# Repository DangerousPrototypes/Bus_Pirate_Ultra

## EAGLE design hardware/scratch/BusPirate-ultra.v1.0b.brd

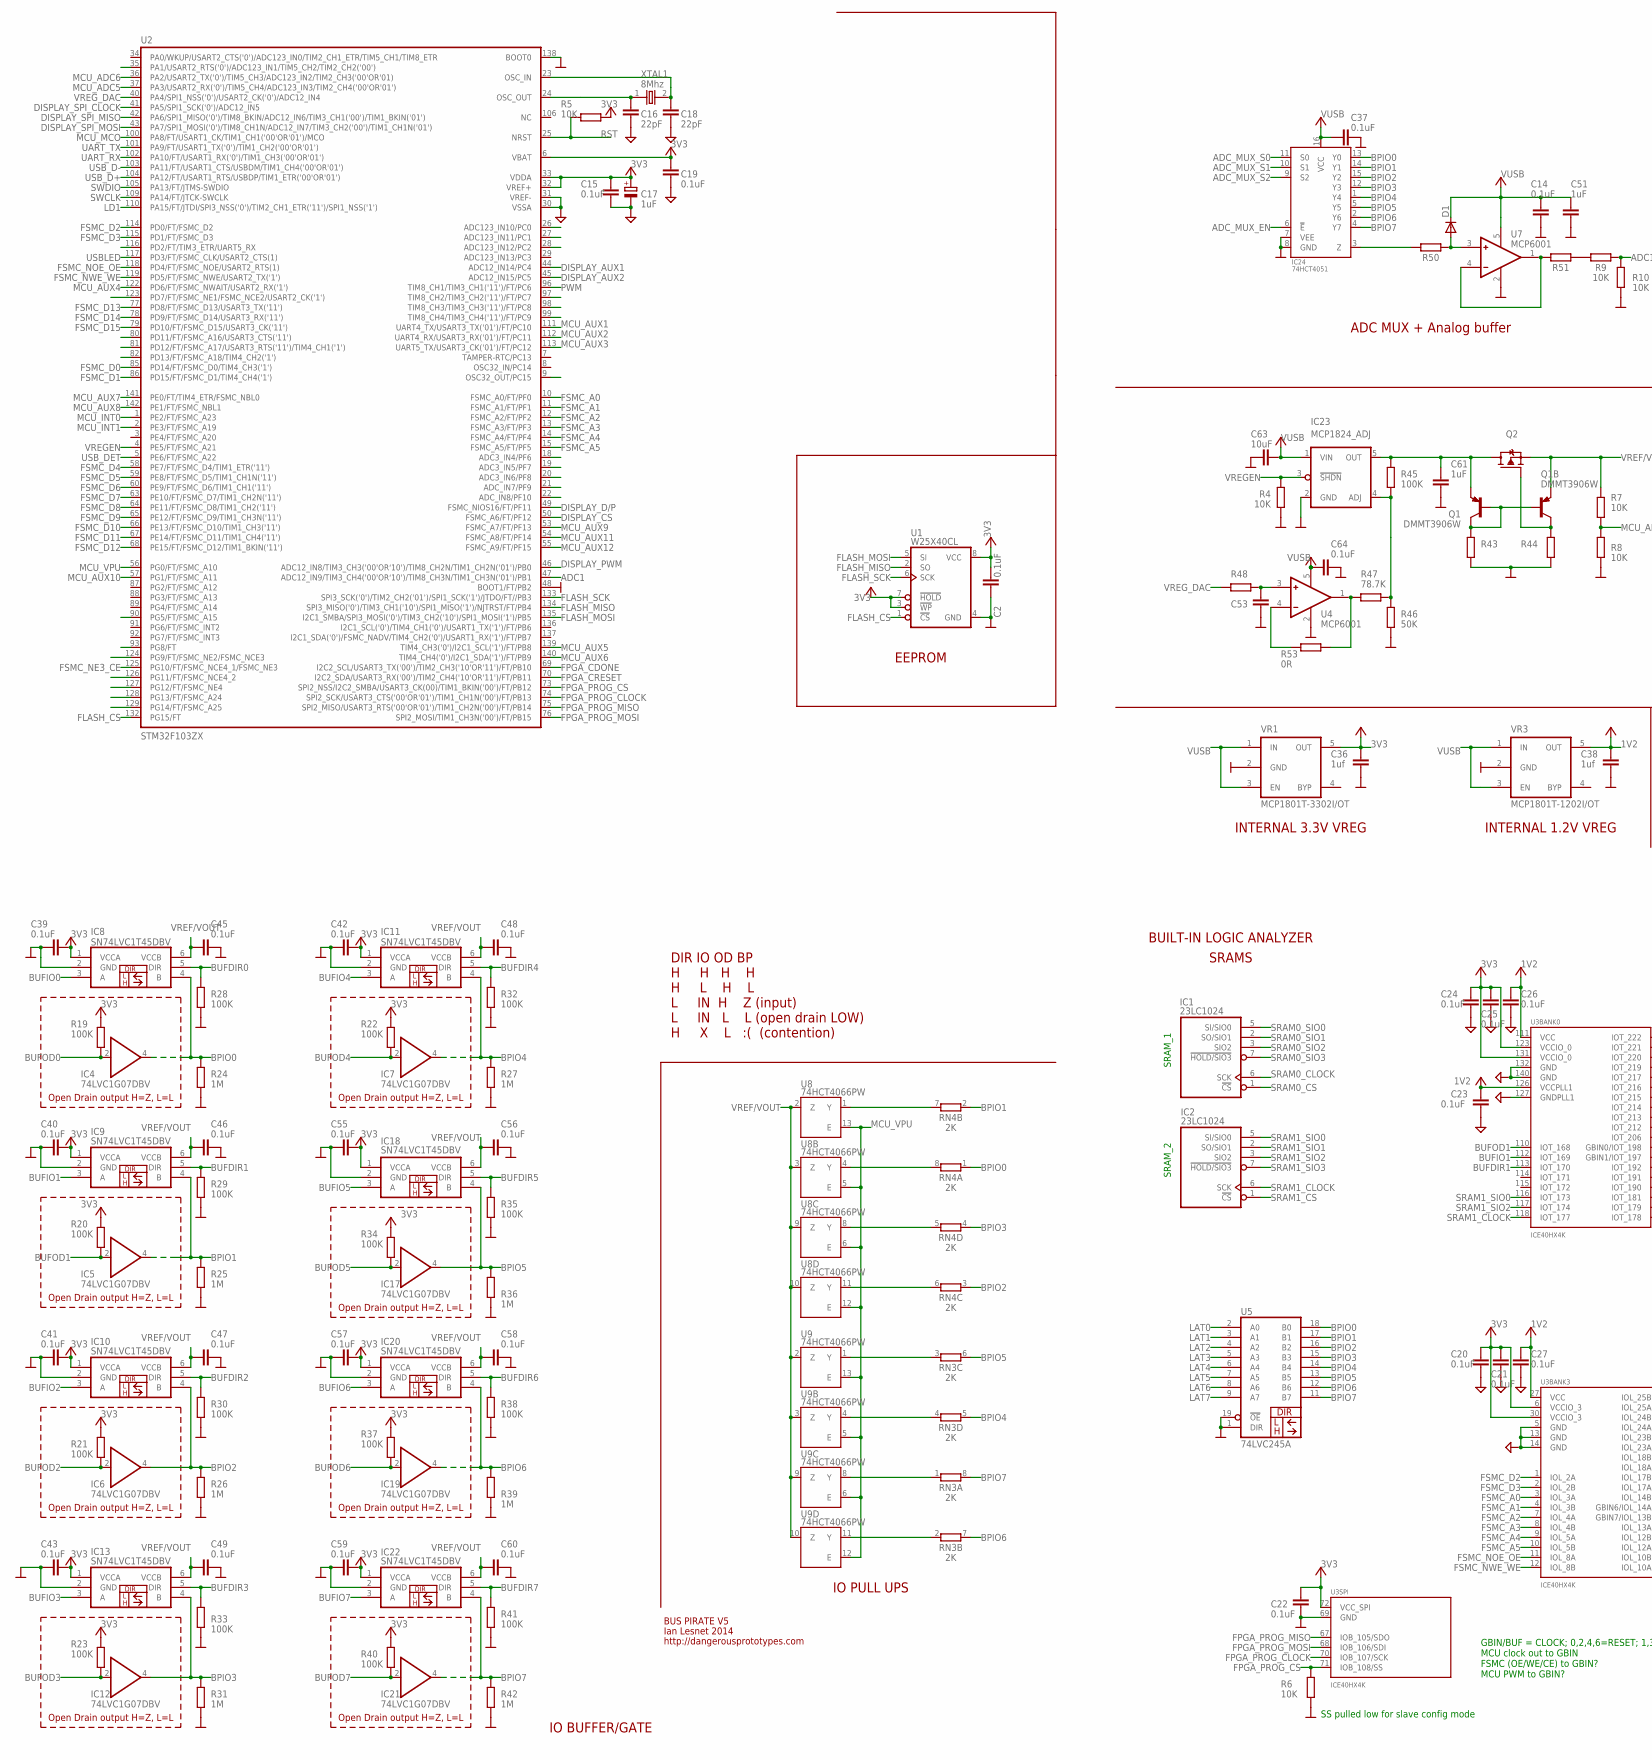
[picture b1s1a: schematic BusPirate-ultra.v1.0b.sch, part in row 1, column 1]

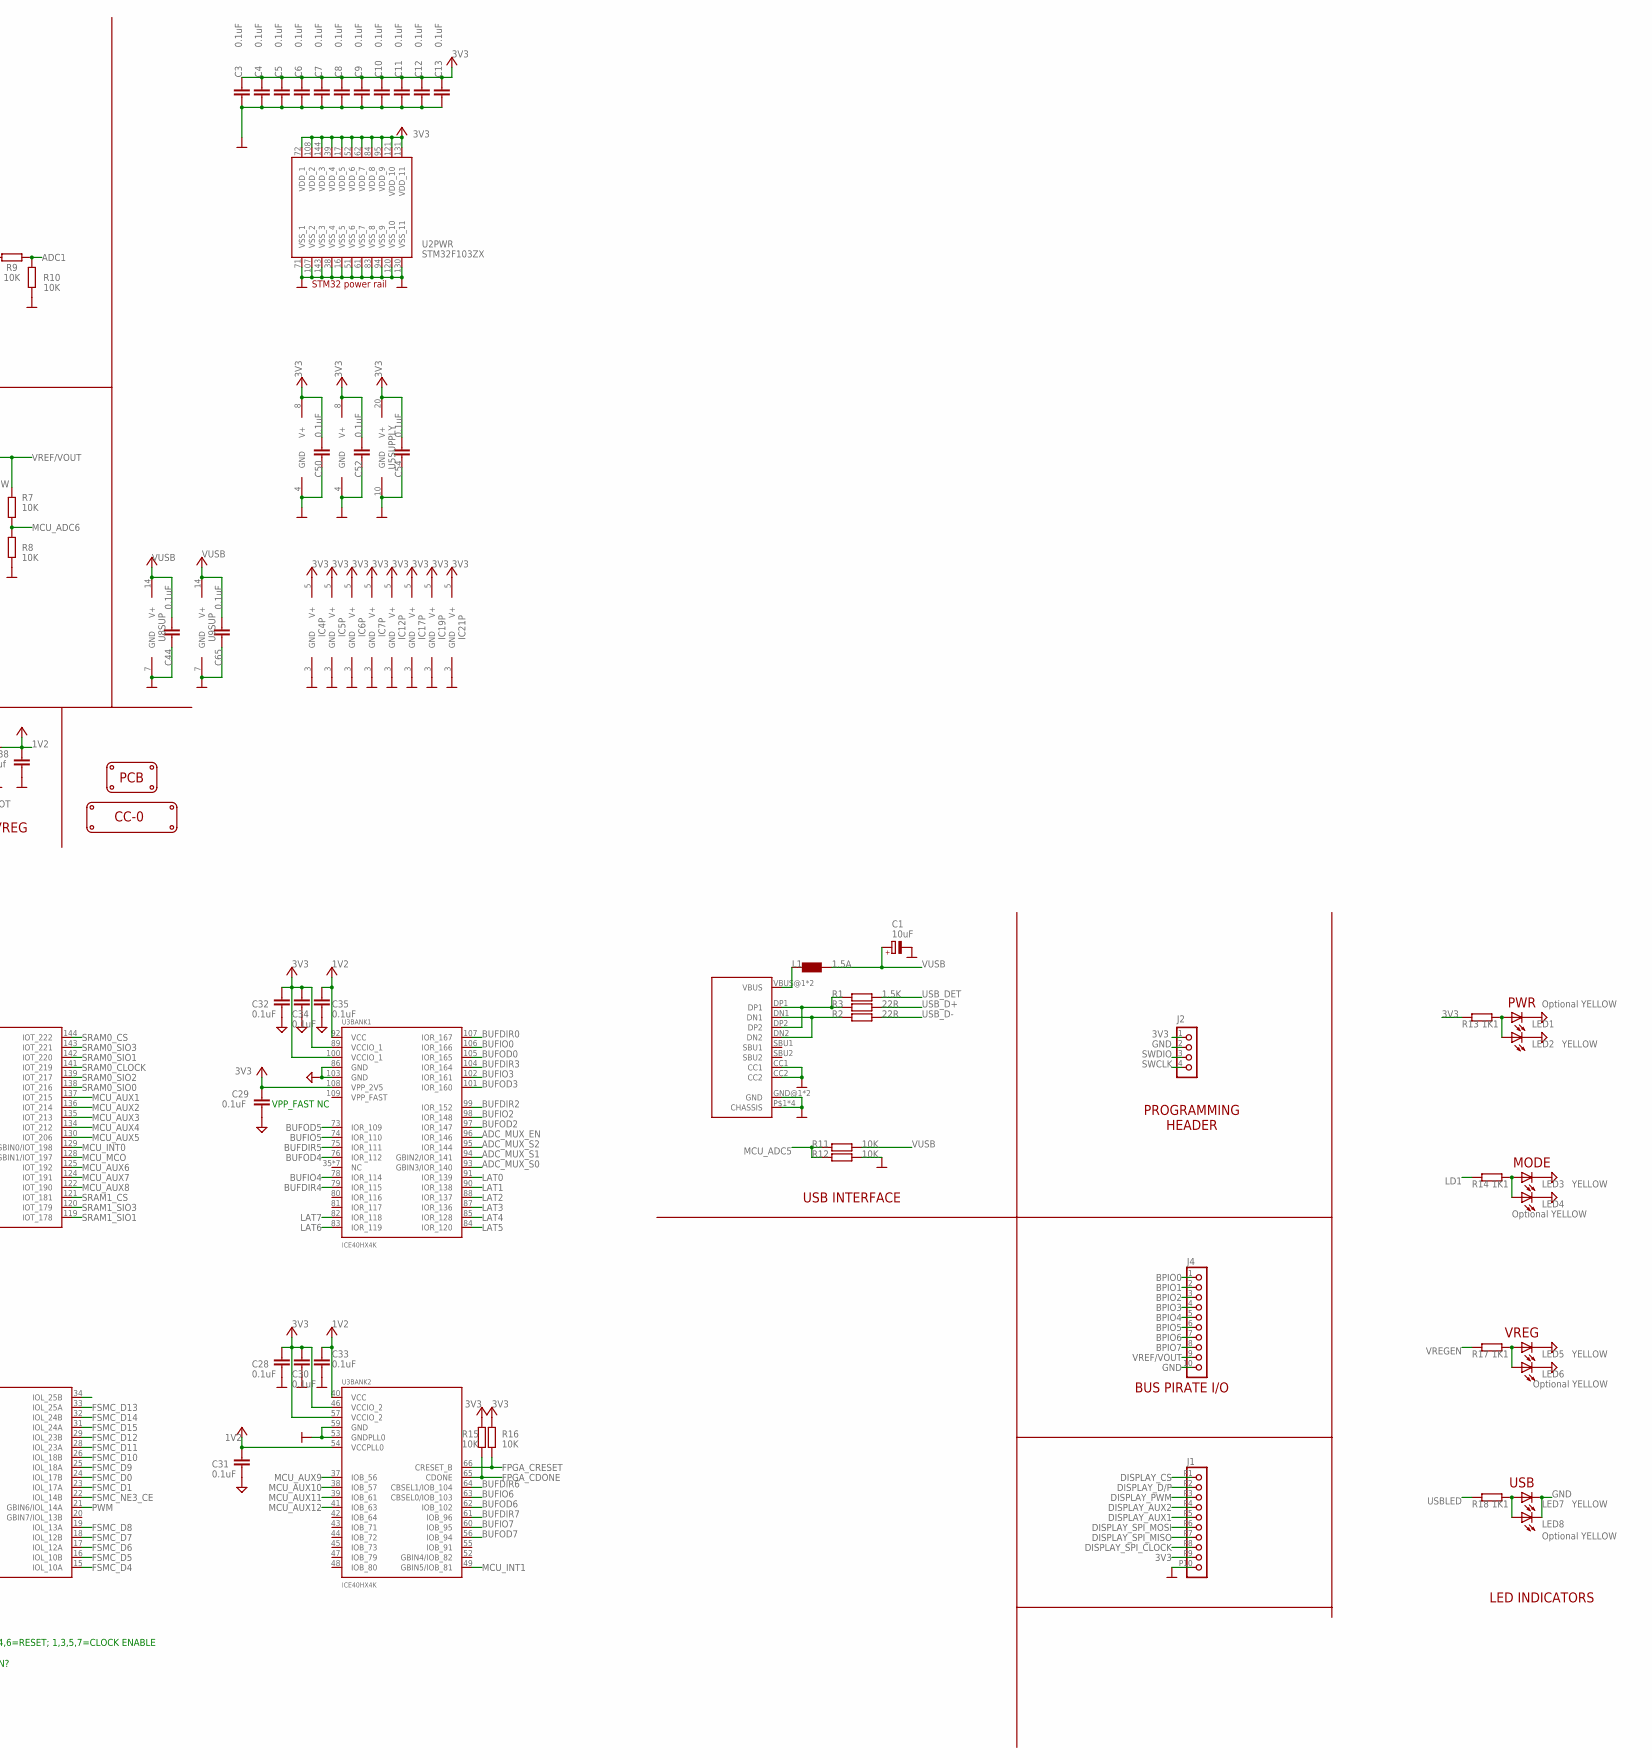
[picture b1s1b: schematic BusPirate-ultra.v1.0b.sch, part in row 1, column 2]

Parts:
C1: 10uF; SMC_A
C2, C3, C4, C5, C6, C7, C8, C9, C11, C12, C13, C14, C15, C19, C21, C22, C23, C24, C25, C26, C28, C29, C30, C31, C32, C33, C34, C35, C37, C44, C50, C52, C54, C65: 0.1uF; C0603
C10, C20, C27: 0.1uF; C402
C16, C18: 22pF; C0603
C17: 1uF; SMC_A
C36, C38: 1uf; C0603
C39, C40, C41, C42, C43, C45, C46, C47, C48, C49, C55, C56, C57, C58, C59, C60: 0.1uF; C0402
C51: 1uF; C0603
C53: CAPACITOR_NPOL-0603; C603
C61: 1uF; C603
C63: 10uF; C603
C64: 0.1uF; C603
D1: DIODE-SOD-123; SOD-123
IC1, IC2: 23LC1024; SOIC-8
IC4, IC5, IC6, IC7, IC12, IC17, IC19, IC21: 74LVC1G07DBV; SC-70-5_EXTENDED_PADS
IC8, IC9, IC10, IC11, IC13, IC18, IC20, IC22: SN74LVC1T45DBV; SC-70-6_EXTENDED_PADS
IC23: MCP1824_ADJ; SOT-23-5
IC24: 74HCT4051; TSSOP-16
J1: CON_MOLEX_MALE_SMT_SH_1.25; MOLEX_533980771
J2: CON_HEADER_1X04; M1X4
J4: CON_HEADER_1X10-RIGHT_ANGLED_PTH_SHROUDED; M1X10_MALE_RIGHT_ANGLES_PTH_SHROUDED
L1: 1.5A; WE-KI_0805_B
LED1, LED4, LED6, LED8: Optional YELLOW; LED-805
LED2, LED3, LED5, LED7: YELLOW; LED-805
LOGO1: LOGO_CC-0
PCB1: PCB_DP_RECTANGLE-50X100; DP10050_V1
Q1: DMMT3906W; SOT-363
Q2: TRANSISTOR_FET_TSM2301CX; SOT-23
R1: 1.5K; R0603
R2, R3: 22R; R0603
R4, R5, R6: 10K; R603
R7, R8, R9, R10, R11, R12, R15, R16: 10K; R0603
R13, R14, R17, R18: 1K1; R603
R19, R20, R21, R22, R23, R28, R29, R30, R32, R33, R34, R35, R37, R38, R40, R41: 100K; R0402
R24, R25, R26, R27, R31, R36, R39, R42: 1M; R0402
R43, R44, R48: RESISTOR-0603; R603
R45: 100K; R603
R46: 50K; R603
R47: 78.7K; R603
R50, R51: R-EU_R0603; R0603
R53: 0R; R603
RN3, RN4: 2K; RN8P-4R-CRA06S
U1: W25X40CL; SOIC-8
U2: STM32F103ZX; TQFP-144
U3: ICE40HX4K; TQFP-144
U4, U7: MCP6001; SOT-23-5
U5: 74LVC245A; TSSOP-20
U8, U9: 74HCT4066PW; TSSOP-14
U$3: USB-C-12; C-31-M-12
VR1: MCP1801T-3302I/OT; SOT-23-5@1
VR3: MCP1801T-1202I/OT; SOT-23-5@1
XTAL1: 8Mhz; XTAL_4X6

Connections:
1V2: C23.2, C26.2, C27.1, C31.2, C33.2, C35.2, C38.1, U3.27 (VCC), U3.40 (VCC), U3.54 (VCCPLL0), U3.92 (VCC), U3.111 (VCC), U3.126 (VCCPLL1), VR3.5 (OUT)
3V3: C2.2, C3.2, C4.2, C5.2, C6.2, C7.2, C8.2, C9.2, C10.1, C11.2, C12.2, C13.2, C15.2, C17.+, C19.2, C20.1, C21.2, C22.2, C24.2, C25.2, C28.2, C29.2, C30.2, C32.2, C34.2, C36.1, C39.1, C40.1, C41.1, C42.1, C43.1, C50.1, C52.1, C54.1, C55.1, C57.1, C59.1, IC1.8 (V+), IC2.8 (V+), IC4.5 (V+), IC5.5 (V+), IC6.5 (V+), IC7.5 (V+), IC8.1 (VCCA), IC9.1 (VCCA), IC10.1 (VCCA), IC11.1 (VCCA), IC12.5 (V+), IC13.1 (VCCA), IC17.5 (V+), IC18.1 (VCCA), IC19.5 (V+), IC20.1 (VCCA), IC21.5 (V+), IC22.1 (VCCA), J1.P9 (9), J2.1, R5.2, R13.2, R15.2, R16.2, R19.2, R20.2, R21.2, R22.2, R23.2, R34.2, R37.2, R40.2, U1.3 (!WP), U1.7 (!HOLD), U1.8 (VCC), U2.6 (VBAT), U2.17 (VDD_5), U2.32 (VREF+), U2.33 (VDDA), U2.39 (VDD_4), U2.52 (VDD_6), U2.62 (VDD_7), U2.72 (VDD_1), U2.84 (VDD_8), U2.95 (VDD_9), U2.108 (VDD_2), U2.121 (VDD_10), U2.131 (VDD_11), U2.144 (VDD_3), U3.6 (VCCIO_3), U3.30 (VCCIO_3), U3.46 (VCCIO_2), U3.57 (VCCIO_2), U3.72 (VCC_SPI), U3.89 (VCCIO_1), U3.100 (VCCIO_1), U3.108 (VPP_2V5), U3.123 (VCCIO_0), U3.131 (VCCIO_0), U5.20 (V+), VR1.5 (OUT)
ADC1: R9.2, R10.2, U2.47 (ADC12_IN9/TIM3_CH4('00'OR'10')/TIM8_CH3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)
ADC_MUX_EN: IC24.6 (!E), U3.96 (IOR_146)
ADC_MUX_S0: IC24.11 (S0), U3.93 (GBIN3/IOR_140)
ADC_MUX_S1: IC24.10 (S1), U3.94 (GBIN2/IOR_141)
ADC_MUX_S2: IC24.9 (S2), U3.95 (IOR_144)
BPIO0: IC4.4 (O), IC8.4 (B), IC24.13 (Y0), J4.1, R24.2, RN4.1, U5.18 (B0)
BPIO1: IC5.4 (O), IC9.4 (B), IC24.14 (Y1), J4.2, R25.2, RN4.2 (1), U5.17 (B1)
BPIO2: IC6.4 (O), IC10.4 (B), IC24.15 (Y2), J4.3, R26.2, RN4.3 (1), U5.16 (B2)
BPIO3: IC12.4 (O), IC13.4 (B), IC24.12 (Y3), J4.4, R31.2, RN4.4 (1), U5.15 (B3)
BPIO4: IC7.4 (O), IC11.4 (B), IC24.1 (Y4), J4.5, R27.2, RN3.5 (2), U5.14 (B4)
BPIO5: IC17.4 (O), IC18.4 (B), IC24.5 (Y5), J4.6, R36.2, RN3.6 (2), U5.13 (B5)
BPIO6: IC19.4 (O), IC20.4 (B), IC24.2 (Y6), J4.7, R39.2, RN3.7 (2), U5.12 (B6)
BPIO7: IC21.4 (O), IC22.4 (B), IC24.4 (Y7), J4.8, R42.2, RN3.8 (2), U5.11 (B7)
BUFDIR0: IC8.5 (DIR), R28.2, U3.107 (IOR_167)
BUFDIR1: IC9.5 (DIR), R29.2, U3.113 (IOT_170)
BUFDIR2: IC10.5 (DIR), R30.2, U3.99 (IOR_152)
BUFDIR3: IC13.5 (DIR), R33.2, U3.104 (IOR_164)
BUFDIR4: IC11.5 (DIR), R32.2, U3.79 (IOR_115)
BUFDIR5: IC18.5 (DIR), R35.2, U3.75 (IOR_111)
BUFDIR6: IC20.5 (DIR), R38.2, U3.64 (CBSEL1/IOB_104)
BUFDIR7: IC22.5 (DIR), R41.2, U3.61 (IOB_96)
BUFIO0: IC8.3 (A), U3.106 (IOR_166)
BUFIO1: IC9.3 (A), U3.112 (IOT_169)
BUFIO2: IC10.3 (A), U3.98 (IOR_148)
BUFIO3: IC13.3 (A), U3.102 (IOR_161)
BUFIO4: IC11.3 (A), U3.78 (IOR_114)
BUFIO5: IC18.3 (A), U3.74 (IOR_110)
BUFIO6: IC20.3 (A), U3.63 (CBSEL0/IOB_103)
BUFIO7: IC22.3 (A), U3.60 (IOB_95)
BUFOD0: IC4.2 (I), R19.1, U3.105 (IOR_165)
BUFOD1: IC5.2 (I), R20.1, U3.110 (IOT_168)
BUFOD2: IC6.2 (I), R21.1, U3.97 (IOR_147)
BUFOD3: IC12.2 (I), R23.1, U3.101 (IOR_160)
BUFOD4: IC7.2 (I), R22.1, U3.76 (IOR_112)
BUFOD5: IC17.2 (I), R34.1, U3.73 (IOR_109)
BUFOD6: IC19.2 (I), R37.1, U3.62 (IOB_102)
BUFOD7: IC21.2 (I), R40.1, U3.56 (IOB_94)
D+: R1.1, R3.2, U$3.DP1, U$3.DP2
D-: R2.2, U$3.DN1, U$3.DN2
DISPLAY_AUX1: J1.P5 (5), U2.44 (ADC12_IN14/PC4)
DISPLAY_AUX2: J1.P4 (4), U2.45 (ADC12_IN15/PC5)
DISPLAY_CS: J1.P1 (1), U2.50 (FSMC_A6/FT/PF12)
DISPLAY_D/P: J1.P2 (2), U2.49 (FSMC_NIOS16/FT/PF11)
DISPLAY_PWM: J1.P3 (3), U2.46 (ADC12_IN8/TIM3_CH3('00'OR'10')/TIM8_CH2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)
DISPLAY_SPI_CLOCK: J1.P8 (8), U2.41 (PA5/SPI1_SCK('0')/ADC12_IN5)
DISPLAY_SPI_MISO: J1.P7 (7), U2.42 (PA6/SPI1_MISO('0')/TIM8_BKIN/ADC12_IN6/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)
DISPLAY_SPI_MOSI: J1.P6 (6), U2.43 (PA7/SPI1_MOSI('0')/TIM8_CH1N/ADC12_IN7/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)
FLASH_CS: U1.1 (!CS), U2.132 (PG15/FT)
FLASH_MISO: U1.2 (SO), U2.134 (SPI3_MISO('0')/TIM3_CH1('10')/SPI1_MISO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)
FLASH_MOSI: U1.5 (SI), U2.135 (I2C1_SMBA/SPI3_MOSI('0')/TIM3_CH2('10')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)
FLASH_SCK: U1.6 (SCK), U2.133 (SPI3_SCK('0')/TIM2_CH2('01')/SPI1_SCK('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)
FPGA_CDONE: R15.1, U2.69 (I2C2_SCL/USART3_TX('00')/TIM2_CH3('10'O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), U3.65 (CDONE)
FPGA_CRESET: R16.1, U2.70 (I2C2_SDA/USART3_RX('00')/TIM2_CH4('10'O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), U3.66 (CRESET_B)
FPGA_PROG_CLOCK: U2.74 (SPI2_SCK/USART3_CTS('00'OR'01')/TIM1_CH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), U3.70 (IOB_107/SCK)
FPGA_PROG_CS: R6.1, U2.73 (SPI2_NSS/I2C2_SMBA/USART3_CK(00)/TIM1_B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), U3.71 (IOB_108/SS)
FPGA_PROG_MISO: U2.75 (SPI2_MISO/USART3_RTS('00'OR'01')/TIM1_C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), U3.67 (IOB_105/SDO)
FPGA_PROG_MOSI: U2.76 (SPI2_MOSI/TIM1_CH3N('00')/FT/PB15), U3.68 (IOB_106/SDI)
FSMC_A0: U2.10 (FSMC_A0/FT/PF0), U3.3 (IOL_3A)
FSMC_A1: U2.11 (FSMC_A1/FT/PF1), U3.4 (IOL_3B)
FSMC_A2: U2.12 (FSMC_A2/FT/PF2), U3.7 (IOL_4A)
FSMC_A3: U2.13 (FSMC_A3/FT/PF3), U3.8 (IOL_4B)
FSMC_A4: U2.14 (FSMC_A4/FT/PF4), U3.9 (IOL_5A)
FSMC_A5: U2.15 (FSMC_A5/FT/PF5), U3.10 (IOL_5B)
FSMC_D0: U2.85 (PD14/FT/FSMC_D0/TIM4_CH3('1')), U3.24 (IOL_17B)
FSMC_D1: U2.86 (PD15/FT/FSMC_D1/TIM4_CH4('1')), U3.23 (IOL_17A)
FSMC_D2: U2.114 (PD0/FT/FSMC_D2), U3.1 (IOL_2A)
FSMC_D3: U2.115 (PD1/FT/FSMC_D3), U3.2 (IOL_2B)
FSMC_D4: U2.58 (PE7/FT/FSMC_D4/TIM1_ETR('11')), U3.15 (IOL_10A)
FSMC_D5: U2.59 (PE8/FT/FSMC_D5/TIM1_CH1N('11')), U3.16 (IOL_10B)
FSMC_D6: U2.60 (PE9/FT/FSMC_D6/TIM1_CH1('11')), U3.17 (IOL_12A)
FSMC_D7: U2.63 (PE10/FT/FSMC_D7/TIM1_CH2N('11')), U3.18 (IOL_12B)
FSMC_D8: U2.64 (PE11/FT/FSMC_D8/TIM1_CH2('11')), U3.19 (IOL_13A)
FSMC_D9: U2.65 (PE12/FT/FSMC_D9/TIM1_CH3N('11')), U3.25 (IOL_18A)
FSMC_D10: U2.66 (PE13/FT/FSMC_D10/TIM1_CH3('11')), U3.26 (IOL_18B)
FSMC_D11: U2.67 (PE14/FT/FSMC_D11/TIM1_CH4('11')), U3.28 (IOL_23A)
FSMC_D12: U2.68 (PE15/FT/FSMC_D12/TIM1_BKIN('11')), U3.29 (IOL_23B)
FSMC_D13: U2.77 (PD8/FT/FSMC_D13/USART3_TX('11')), U3.33 (IOL_25A)
FSMC_D14: U2.78 (PD9/FT/FSMC_D14/USART3_RX('11')), U3.32 (IOL_24B)
FSMC_D15: U2.79 (PD10/FT/FSMC_D15/USART3_CK('11')), U3.31 (IOL_24A)
FSMC_NE3_CE: U2.125 (PG10/FT/FSMC_NCE4_1/FSMC_NE3), U3.22 (IOL_14B)
FSMC_NOE_OE: U2.118 (PD4/FT/FSMC_NOE/USART2_RTS(1)), U3.11 (IOL_8A)
FSMC_NWE_WE: U2.119 (PD5/FT/FSMC_NWE/USART2_TX('1')), U3.12 (IOL_8B)
GND: C1.-, C2.1, C3.1, C4.1, C5.1, C6.1, C7.1, C8.1, C9.1, C10.2, C11.1, C12.1, C13.1, C14.2, C15.1, C16.1, C17.-, C18.1, C19.1, C20.2, C21.1, C22.1, C23.1, C24.1, C25.1, C26.1, C27.2, C28.1, C29.1, C30.1, C31.1, C32.1, C33.1, C34.1, C35.1, C36.2, C37.2, C38.2, C39.2, C40.2, C41.2, C42.2, C43.2, C44.2, C45.1, C46.1, C47.1, C48.1, C49.1, C50.2, C51.2, C52.2, C53.2, C54.2, C55.2, C56.1, C57.2, C58.1, C59.2, C60.1, C61.2, C63.2, C64.2, C65.2, IC1.4 (GND), IC2.4 (GND), IC4.3 (GND), IC5.3 (GND), IC6.3 (GND), IC7.3 (GND), IC8.2 (GND), IC9.2 (GND), IC10.2 (GND), IC11.2 (GND), IC12.3 (GND), IC13.2 (GND), IC17.3 (GND), IC18.2 (GND), IC19.3 (GND), IC20.2 (GND), IC21.3 (GND), IC22.2 (GND), IC23.2 (GND), IC24.7 (VEE), IC24.8 (GND), J1.P10 (10), J2.2, J4.10, LED1.C, LED2.C, LED3.C, LED4.C, LED5.C, LED6.C, LED7.C, LED8.C, R4.2, R6.2, R8.1, R10.1, R12.1, R24.1, R25.1, R26.1, R27.1, R28.1, R29.1, R30.1, R31.1, R32.1, R33.1, R35.1, R36.1, R38.1, R39.1, R41.1, R42.1, R43.1, R44.1, R46.2, U1.4 (GND), U2.16 (VSS_5), U2.30 (VSSA), U2.31 (VREF-), U2.38 (VSS_4), U2.48 (BOOT1/FT/PB2), U2.51 (VSS_6), U2.61 (VSS_7), U2.71 (VSS_1), U2.83 (VSS_8), U2.94 (VSS_9), U2.107 (VSS_2), U2.120 (VSS_10), U2.130 (VSS_11), U2.138 (BOOT0), U2.143 (VSS_3), U3.5 (GND), U3.13 (GND), U3.14 (GND), U3.53 (GNDPLL0), U3.59 (GND), U3.69 (GND), U3.86 (GND), U3.103 (GND), U3.127 (GNDPLL1), U3.132 (GND), U3.140 (GND), U4.2 (V-), U5.1 (DIR), U5.10 (GND), U5.19 (!OE), U7.2 (V-), U8.7 (GND), U9.7 (GND), U$3.CC1, U$3.CC2, U$3.GND@1 (GND), U$3.GND@2 (GND), U$3.P$1 (CHASSIS), U$3.P$2 (CHASSIS), U$3.P$3 (CHASSIS), U$3.P$4 (CHASSIS), VR1.2 (GND), VR3.2 (GND)
LAT0: U3.91 (IOR_139), U5.2 (A0)
LAT1: U3.90 (IOR_138), U5.3 (A1)
LAT2: U3.88 (IOR_137), U5.4 (A2)
LAT3: U3.87 (IOR_136), U5.5 (A3)
LAT4: U3.85 (IOR_128), U5.6 (A4)
LAT5: U3.84 (IOR_120), U5.7 (A5)
LAT6: U3.83 (IOR_119), U5.8 (A6)
LAT7: U3.82 (IOR_118), U5.9 (A7)
LD1: R14.2, U2.110 (PA15/FT/JTDI/SPI3_NSS('0')/TIM2_CH1_ETR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)
MCU_ADC5: R11.2, R12.2, U2.37 (PA3/USART2_RX('0')/TIM5_CH4/ADC123_IN3/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)
MCU_ADC6: R7.2, R8.2, U2.36 (PA2/USART2_TX('0')/TIM5_CH3/ADC123_IN2/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)
MCU_AUX1: U2.111 (UART4_TX/USART3_TX('01')/FT/PC10), U3.137 (IOT_215)
MCU_AUX2: U2.112 (UART4_RX/USART3_RX('01')/FT/PC11), U3.136 (IOT_214)
MCU_AUX3: U2.113 (UART5_TX/USART3_CK('01')/FT/PC12), U3.135 (IOT_213)
MCU_AUX4: U2.122 (PD6/FT/FSMC_NWAIT/USART2_RX('1')), U3.134 (IOT_212)
MCU_AUX5: U2.139 (TIM4_CH3('0')/I2C1_SCL('1')/FT/PB8), U3.130 (IOT_206)
MCU_AUX6: U2.140 (TIM4_CH4('0')/I2C1_SDA('1')/FT/PB9), U3.125 (IOT_192)
MCU_AUX7: U2.141 (PE0/FT/TIM4_ETR/FSMC_NBL0), U3.124 (IOT_191)
MCU_AUX8: U2.142 (PE1/FT/FSMC_NBL1), U3.122 (IOT_190)
MCU_AUX9: U2.53 (FSMC_A7/FT/PF13), U3.37 (IOB_56)
MCU_AUX10: U2.57 (PG1/FT/FSMC_A11), U3.38 (IOB_57)
MCU_AUX11: U2.54 (FSMC_A8/FT/PF14), U3.39 (IOB_61)
MCU_AUX12: U2.55 (FSMC_A9/FT/PF15), U3.41 (IOB_63)
MCU_INT0: U2.1 (PE2/FT/FSMC_A23), U3.129 (GBIN0/IOT_198)
MCU_INT1: U2.2 (PE3/FT/FSMC_A19), U3.49 (GBIN5/IOB_81)
MCU_MCO: U2.100 (PA8/FT/USART1_CK/TIM1_CH1('00'OR'01')/M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), U3.128 (GBIN1/IOT_197)
MCU_VPU: U2.56 (PG0/FT/FSMC_A10), U8.5 (E), U8.6 (E), U8.12 (E), U8.13 (E), U9.5 (E), U9.6 (E), U9.12 (E), U9.13 (E)
unnamed: L1.2 (1), U$3.VBUS@1 (VBUS), U$3.VBUS@2 (VBUS)
unnamed: RN4.7 (2), U8.1 (Y)
unnamed: RN4.8 (2), U8.4 (Y)
unnamed: RN4.5 (2), U8.8 (Y)
unnamed: RN4.6 (2), U8.11 (Y)
unnamed: LED3.A, LED4.A, R14.1
unnamed: LED1.A, LED2.A, R13.1
unnamed: C18.2, U2.23 (OSC_IN), XTAL1.2
unnamed: C16.2, U2.24 (OSC_OUT), XTAL1.1
unnamed: Q1.6 (C), Q2.1 (G), R44.2
unnamed: IC23.4 (ADJ), R45.1, R46.1, R47.2
unnamed: LED7.A, LED8.A, R18.1
unnamed: R53.1, U4.4 (-)
unnamed: LED5.A, LED6.A, R17.1
unnamed: R47.1, R53.2, U4.1 (OUT)
unnamed: C61.1, IC23.5 (OUT), Q1.4 (E), Q2.3 (D), R45.2
unnamed: Q1.1 (B), Q1.2 (B), Q1.3 (C), R43.2
unnamed: C53.1, R48.2, U4.3 (+)
unnamed: D1.A, R50.2, U7.3 (+)
unnamed: RN3.3 (1), U9.1 (Y)
unnamed: RN3.4 (1), U9.4 (Y)
unnamed: RN3.1, U9.8 (Y)
unnamed: RN3.2 (1), U9.11 (Y)
unnamed: IC24.3 (Z), R50.1
unnamed: R51.1, U7.1 (OUT), U7.4 (-)
unnamed: R9.1, R51.2
PWM: U2.96 (TIM8_CH1/TIM3_CH1('11')/FT/PC6), U3.21 (GBIN6/IOL_14A)
RST: R5.1, U2.25 (NRST)
SRAM0_CLOCK: IC1.6 (SCK), U3.141 (IOT_219)
SRAM0_CS: IC1.1 (!CS), U3.144 (IOT_222)
SRAM0_SIO0: IC1.5 (SI/SIO0), U3.138 (IOT_216)
SRAM0_SIO1: IC1.2 (SO/SIO1), U3.142 (IOT_220)
SRAM0_SIO2: IC1.3 (SIO2), U3.139 (IOT_217)
SRAM0_SIO3: IC1.7 (!HOLD/SIO3), U3.143 (IOT_221)
SRAM1_CLOCK: IC2.6 (SCK), U3.118 (IOT_177)
SRAM1_CS: IC2.1 (!CS), U3.121 (IOT_181)
SRAM1_SIO0: IC2.5 (SI/SIO0), U3.116 (IOT_173)
SRAM1_SIO1: IC2.2 (SO/SIO1), U3.119 (IOT_178)
SRAM1_SIO2: IC2.3 (SIO2), U3.117 (IOT_174)
SRAM1_SIO3: IC2.7 (!HOLD/SIO3), U3.120 (IOT_179)
SWCLK: J2.4, U2.109 (PA14/FT/JTCK-SWCLK)
SWDIO: J2.3, U2.105 (PA13/FT/JTMS-SWDIO)
UART_RX: U2.102 (PA10/FT/USART1_RX('0')/TIM1_CH3('00'OR'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)
UART_TX: U2.101 (PA9/FT/USART1_TX('0')/TIM1_CH2('00'OR'0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)
USBLED: R18.2, U2.117 (PD3/FT/FSMC_CLK/USART2_CTS(1))
USB_D+: R3.1, U2.104 (PA12/FT/USART1_RTS/USBDP/TIM1_ETR('00'O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)
USB_D-: R2.1, U2.103 (PA11/FT/USART1_CTS/USBDM/TIM1_CH4('00'O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)
USB_DET: R1.2, U2.5 (PE6/FT/FSMC_A22)
VPP_FAST: U3.109 (VPP_FAST)
VREF/VOUT: C45.2, C46.2, C47.2, C48.2, C49.2, C56.2, C58.2, C60.2, IC8.6 (VCCB), IC9.6 (VCCB), IC10.6 (VCCB), IC11.6 (VCCB), IC13.6 (VCCB), IC18.6 (VCCB), IC20.6 (VCCB), IC22.6 (VCCB), J4.9, Q1.5 (E), Q2.2 (S), R7.1, U8.2 (Z), U8.3 (Z), U8.9 (Z), U8.10 (Z), U9.2 (Z), U9.3 (Z), U9.9 (Z), U9.10 (Z)
VREGEN: IC23.3 (!SHDN), R4.1, R17.2, U2.4 (PE5/FT/FSMC_A21)
VREG_DAC: R48.1, U2.40 (PA4/SPI1_NSS('0')/USART2_CK('0')/ADC12_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)
VUSB: C1.+, C14.1, C37.1, C44.1, C51.1, C63.1, C64.1, C65.1, D1.C, IC23.1 (VIN), IC24.16 (VCC), L1.1 (2), R11.1, U4.5 (V+), U7.5 (V+), U8.14 (V+), U9.14 (V+), VR1.1 (IN), VR1.3 (EN), VR3.1 (IN), VR3.3 (EN)

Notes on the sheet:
BUS PIRATE V5
Ian Lesnet 2014
http://dangerousprototypes.com
SRAMS
IO BUFFER/GATE
BUS PIRATE I/O
PWR
MODE
VREG
PROGRAMMING HEADER
USB
INTERNAL 3.3V VREG
BUILT-IN LOGIC ANALYZER
ADC MUX + Analog buffer
USB INTERFACE
IO PULL UPS
LED INDICATORS
Open Drain output H=Z, L=L
SS pulled low for slave config mode
VPP_FAST NC
GBIN/BUF = CLOCK; 0,2,4,6=RESET; 1,3,5,7=CLOCK ENABLE MCU clock out to GBIN FSMC (OE/WE/CE) to GBIN? MCU PWM to GBIN?
DIR IO OD BP H H H H H L H L L IN H Z (input) L IN L L (open drain LOW) H X L :( (contention)
STM32 power rail
INTERNAL 1.2V VREG
SRAM_1
SRAM_2
EEPROM

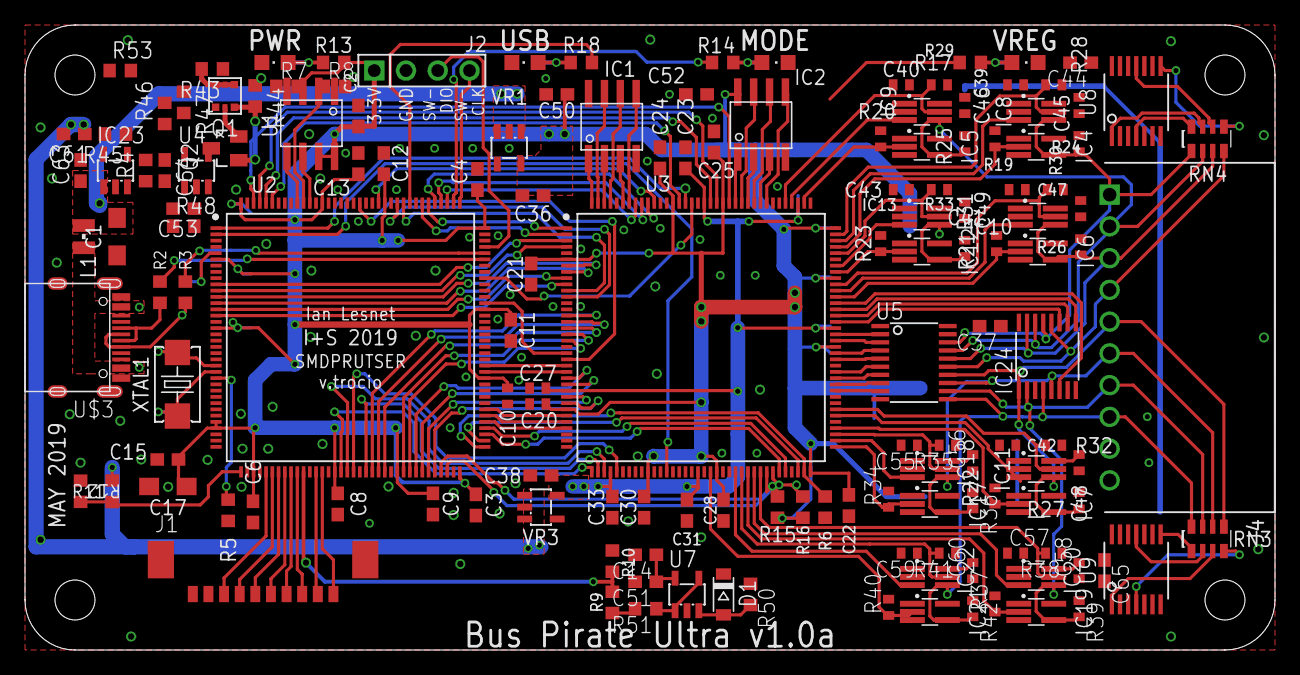
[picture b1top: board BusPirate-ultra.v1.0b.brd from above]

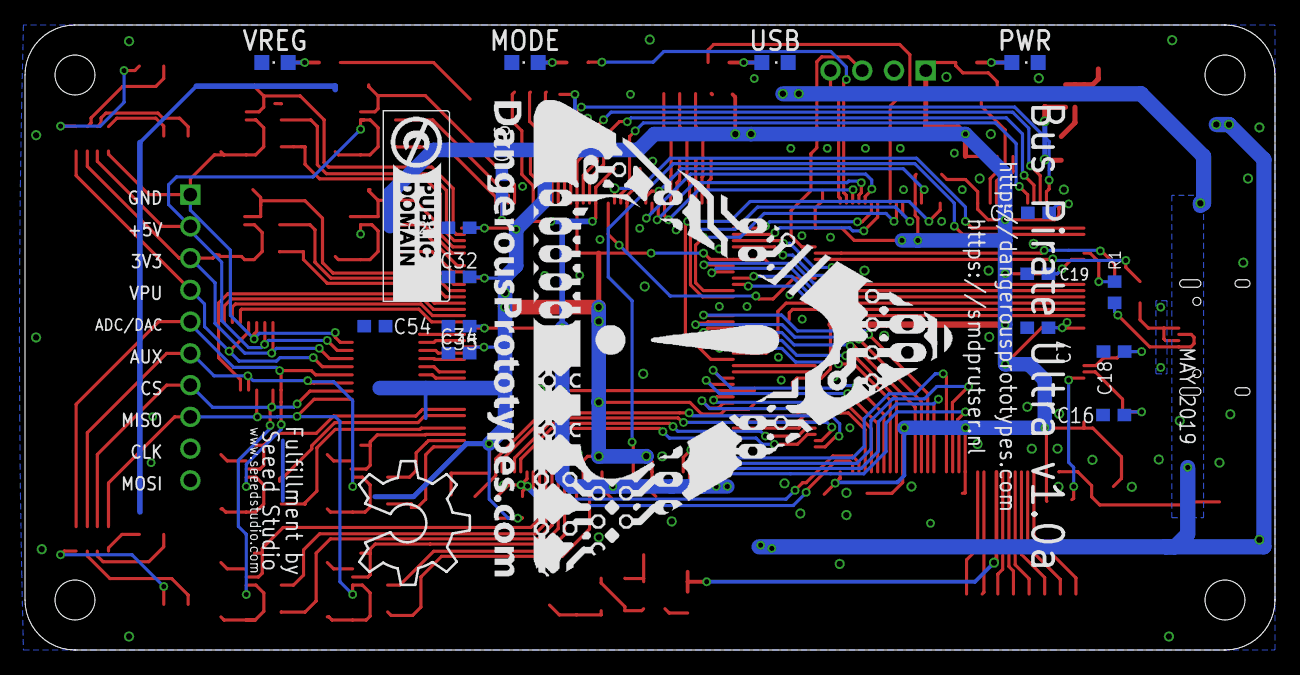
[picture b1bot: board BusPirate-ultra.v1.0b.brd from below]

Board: 2 copper layers, 100.0 x 50.0 mm, 169 parts (19 on the bottom side), 162 nets.

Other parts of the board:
U$1: DP-LOGO
U$2: OSHW_8X350_NOTEXT
U$4: DP_LOGO_ART_1.5X1.5

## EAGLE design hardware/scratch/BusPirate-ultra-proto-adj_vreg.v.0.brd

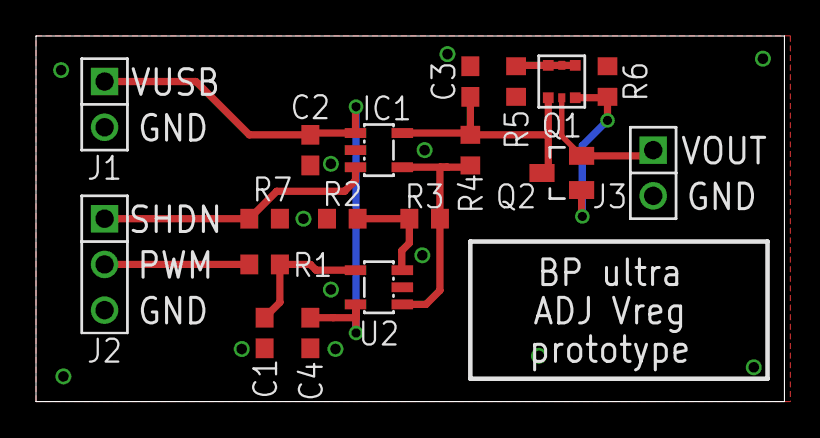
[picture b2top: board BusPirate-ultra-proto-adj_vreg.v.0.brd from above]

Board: 2 copper layers, 41.6 x 20.3 mm, 19 parts (0 on the bottom side), 11 nets.

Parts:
C1, C2, C4: 0.1uF; C603
C3: 1uF; C603
IC1: MCP1824_ADJ; SOT-23-5
J1, J3: CON_HEADER_1X02-PTH; M1X2
J2: CON_HEADER_1X03-PTH; M1X3
PAGE1: FRAME_DINA4_L; DP_LOGO
Q1: DMMT3906W; SOT-363
Q2: SOT-23
R1: 1M; R603
R2, R3, R5, R6: R603
R4: 330R; R603
R7: 10K; R603
U2: MCP6001; SOT-23-5

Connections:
!SHDN: IC1.3, J2.1, R7.1
GND: C1.2, C2.2, C3.2, C4.2, IC1.2, J1.2, J2.3, J3.2, R2.2, R5.1, R6.1, R7.2, U2.2
unnamed: C3.1, IC1.5, Q1.4, Q2.3, R4.2
unnamed: Q1.1, Q1.2, Q1.3, R5.2
unnamed: Q1.6, Q2.1, R6.2
unnamed: IC1.4, R3.1, R4.1, U2.1
unnamed: R2.1, R3.2, U2.3
unnamed: C1.1, R1.1, U2.4
PWM: J2.2, R1.2
VPU: J3.1, Q1.5, Q2.2
VUSB: C2.1, C4.1, IC1.1, J1.1, U2.5

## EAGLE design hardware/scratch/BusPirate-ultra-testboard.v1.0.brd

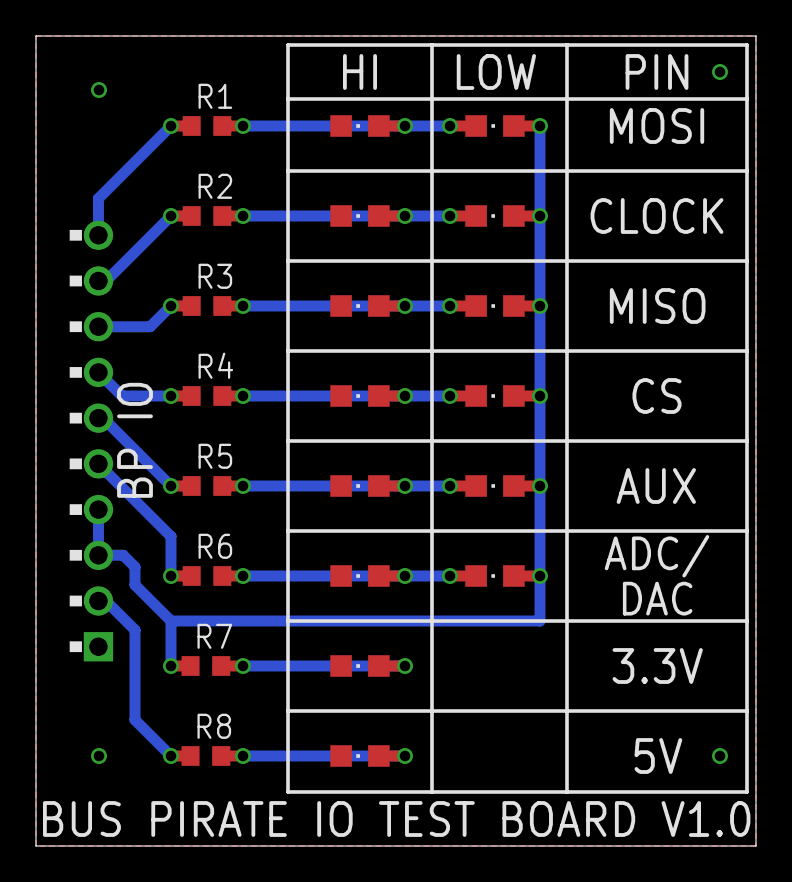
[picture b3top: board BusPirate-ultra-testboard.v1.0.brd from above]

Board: 2 copper layers, 40.0 x 45.0 mm, 24 parts (0 on the bottom side), 17 nets.

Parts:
J1: CON_HEADER_1X10-RIGHT_ANGLED_PTH; M1X10_FEMALE_RIGHT_ANGLED_PTH
LED1, LED2, LED3, LED4, LED5, LED6, LED7, LED8, LED9, LED10, LED11, LED12, LED13, LED14: LED-805
PAGE1: FRAME_DINA4_L; DP_LOGO
R1, R2, R3, R4, R5, R6, R7, R8: 1k1; R603

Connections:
3V3: J1.3, J1.4, LED2.A, LED4.A, LED6.A, LED8.A, LED10.A, LED12.A, R7.1
5V0: J1.2, R8.1
ADC_DAC: J1.5, R6.1
AUX: J1.6, R5.1
CLOCK: J1.9, R2.1
CS: J1.7, R4.1
GND: J1.1, LED1.C, LED3.C, LED5.C, LED7.C, LED9.C, LED11.C, LED13.C, LED14.C
MISO: J1.8, R3.1
MOSI: J1.10, R1.1
unnamed: LED1.A, LED2.C, R1.2
unnamed: LED3.A, LED4.C, R2.2
unnamed: LED5.A, LED6.C, R3.2
unnamed: LED7.A, LED8.C, R4.2
unnamed: LED9.A, LED10.C, R5.2
unnamed: LED11.A, LED12.C, R6.2
unnamed: LED14.A, R8.2
unnamed: LED13.A, R7.2

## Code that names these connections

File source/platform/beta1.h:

// development test platform
#define BP_PLATFORM		"BPULTRA v1.0 may 2019"
#define FIRMWARE_VERSION 	"v8"

// LEDs
#define BP_LED_MODE_PORT	GPIOA
#define BP_LED_MODE_PIN		GPIO15
#define BP_LED_USB_PORT		GPIOD
#define BP_LED_USB_PIN		GPIO3

// debug USART
#define BP_DEBUG_TX_PORT	GPIOB
#define BP_DEBUG_TX_PIN		GPIO6
#define BP_DEBUG_USART		USART1
#define BP_DEBUG_USART_CLK	RCC_USART1

// delay
#define BP_DELAYTIMER		TIM4
#define BP_DELAYTIMER_CLOCK	RCC_TIM4

// usb
#define	BP_USB_PULLUP_PORT	GPIOE
#define BP_USB_PULLUP_PIN	GPIO6

// flash storage
#define BP_FS_SPI		    SPI3
#define BP_FS_SPI_CLK		RCC_SPI3
#define BP_FS_CLK_PIN		GPIO3
#define BP_FS_MOSI_PIN		GPIO5
#define BP_FS_MISO_PIN		GPIO4
#define BP_FS_CS_PIN		GPIO15		// misuse RX pin on debug header?
#define BP_FS_CLK_PORT		GPIOB
#define BP_FS_MOSI_PORT		GPIOB
#define BP_FS_MISO_PORT		GPIOB
#define BP_FS_CS_PORT		GPIOG

// LCD
#define BP_LCD_SPI		    SPI1
#define BP_LCD_SPI_CLK		RCC_SPI1
#define BP_LCD_CLK_PIN		GPIO5
#define BP_LCD_MOSI_PIN	    GPIO7
#define BP_LCD_MISO_PIN	    GPIO6
#define BP_LCD_CS_PIN		GPIO2
#define BP_LCD_DP_PIN      GPIO3
#define BP_LCD_RESET_PIN    GPIO5
#define BP_LCD_AUX2_PIN    GPIO4
#define BP_LCD_CLK_PORT	    GPIOA
#define BP_LCD_MOSI_PORT	GPIOA
#define BP_LCD_MISO_PORT	GPIOA
#define BP_LCD_CS_PORT		GPIOE
#define BP_LCD_DP_PORT      GPIOE
#define BP_LCD_RESET_PORT    GPIOE
#define BP_LCD_AUX2_PORT    GPIOE




// FPGA
#define BP_FPGA_SPI		    SPI2
#define BP_FPGA_SPI_CLK		RCC_SPI2
#define BP_FPGA_CLK_PIN		GPIO13
#define BP_FPGA_MOSI_PIN	GPIO15
#define BP_FPGA_MISO_PIN	GPIO14
#define BP_FPGA_CS_PIN		GPIO12
#define BP_FPGA_CLK_PORT	GPIOB
#define BP_FPGA_MOSI_PORT	GPIOB
#define BP_FPGA_MISO_PORT	GPIOB
#define BP_FPGA_CS_PORT		GPIOB

#define BP_FPGA_CDONE_PIN	GPIO10
#define BP_FPGA_CRESET_PIN	GPIO11
#define BP_FPGA_CDONE_PORT	GPIOB
#define BP_FPGA_CRESET_PORT	GPIOB

#define BP_FPGA_ACTIVE_PORT         GPIOC
#define BP_FPGA_FIFO_IN_FULL_PORT   GPIOC
#define BP_FPGA_FIFO_OUT_NEMPTY_PORT    GPIOC

#define BP_FPGA_ACTIVE_PIN         GPIO10
#define BP_FPGA_FIFO_IN_FULL_PIN   GPIO11
#define BP_FPGA_FIFO_OUT_NEMPTY_PIN    GPIO12

#define BP_FPGA_FIFO_CLEAR_PORT   GPIOD
#define BP_FPGA_FIFO_CLEAR_PIN    GPIO6


/*
mcu_aux1	pc10
mcu_aux2	pc11
mcu_aux3	pc12
mcu_aux4	pd6
mcu_aux5	pb8
mcu_aux6	pb9
mcu_aux7	pe0
mcu_aux8	pe1
mcu_aux9	pf13
mcu_aux10	pb10
mcu_aux11	pc5
mcu_aux12	pa6
mcu_aux		pc5
mcu_int0	pe2
mcu_int1	pe3
*/


// FSMC
#define BP_FSMC_A0_PORT		GPIOF
#define BP_FSMC_A0_PIN		GPIO0
#define BP_FSMC_A1_PORT		GPIOF
#define BP_FSMC_A1_PIN		GPIO1
#define BP_FSMC_A2_PORT		GPIOF
#define BP_FSMC_A2_PIN		GPIO2
#define BP_FSMC_A3_PORT		GPIOF
#define BP_FSMC_A3_PIN		GPIO3
#define BP_FSMC_A4_PORT		GPIOF
#define BP_FSMC_A4_PIN		GPIO4
#define BP_FSMC_A5_PORT		GPIOF
#define BP_FSMC_A5_PIN		GPIO5

#define BP_FSMC_D0_PORT		GPIOD
#define BP_FSMC_D0_PIN		GPIO14
#define BP_FSMC_D1_PORT		GPIOD
#define BP_FSMC_D1_PIN		GPIO15
#define BP_FSMC_D2_PORT		GPIOD
#define BP_FSMC_D2_PIN		GPIO0
#define BP_FSMC_D3_PORT		GPIOD
#define BP_FSMC_D3_PIN		GPIO1

#define BP_FSMC_D4_PORT		GPIOE
#define BP_FSMC_D4_PIN		GPIO7
#define BP_FSMC_D5_PORT		GPIOE
#define BP_FSMC_D5_PIN		GPIO8
#define BP_FSMC_D6_PORT		GPIOE
#define BP_FSMC_D6_PIN		GPIO9
#define BP_FSMC_D7_PORT		GPIOE
#define BP_FSMC_D7_PIN		GPIO10

#define BP_FSMC_D8_PORT		GPIOE
#define BP_FSMC_D8_PIN		GPIO11
#define BP_FSMC_D9_PORT		GPIOE
#define BP_FSMC_D9_PIN		GPIO12
#define BP_FSMC_D10_PORT	GPIOE
#define BP_FSMC_D10_PIN		GPIO13
#define BP_FSMC_D11_PORT	GPIOE
#define BP_FSMC_D11_PIN		GPIO14

#define BP_FSMC_D12_PORT	GPIOE
#define BP_FSMC_D12_PIN		GPIO15
#define BP_FSMC_D13_PORT	GPIOD
#define BP_FSMC_D13_PIN		GPIO8
#define BP_FSMC_D14_PORT	GPIOD
#define BP_FSMC_D14_PIN		GPIO9
#define BP_FSMC_D15_PORT	GPIOD
#define BP_FSMC_D15_PIN		GPIO10

#define BP_FSMC_NOE_PORT	GPIOD
#define BP_FSMC_NOE_PIN		GPIO4
#define BP_FSMC_NWE_PORT	GPIOD
#define BP_FSMC_NWE_PIN		GPIO5
#define BP_FSMC_NCE_PORT	GPIOG
#define BP_FSMC_NCE_PIN		GPIO10




// pullups and poewrsupplies
#define BP_VPUEN_PORT		GPIOG
#define BP_VPUEN_PIN		GPIO0
//#define BP_PSUEN_PORT		GPIOE
//#define BP_PSUEN_PIN		GPIO5

// adc
#define BP_ADC			ADC1
#define BP_ADC_CLK		RCC_ADC1
#define BP_ADC_CHAN		9
#define BP_VOUT_CHAN	2
#define BP_USB_CHAN		3

#define	BP_ADC_PORT		GPIOB
#define	BP_ADC_PIN		GPIO1
#define BP_VSUP_PORT    GPIOA
#define BP_VSUP_PIN		GPIO3
#define BP_VOUT_PORT    GPIOA
#define BP_VOUT_PIN		GPIO2


#define DAC_CLOCK_PORT GPIOC
#define DAC_CLOCK_PIN   GPIO4
#define DAC_DATA_PORT   GPIOB
#define DAC_DATA_PIN    GPIO1
#define DAC_SYNC_PORT   GPIOC
#define DAC_SYNC_PIN    GPIO5

#define CURRENT_INT0_PORT GPIOC
#define CURRENT_INT0_PIN    GPIO1
#define CURRENT_INT1_PORT GPIOC
#define CURRENT_INT1_PIN    GPIO3

#define CURRENT_TEST_PORT   GPIOG
#define CURRENT_TEST_PIN    GPIO5
#define CURRENT_RESET_PORT  GPIOC
#define CURRENT_RESET_PIN   GPIO2

#define VREGEN_PORT GPIOB
#define VREGEN_PIN  GPIO2

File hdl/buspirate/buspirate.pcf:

#------------------------------------------------------------------
#-- Bus Pirate pin map for development hardware
#--
#------------------------------------------------------------------

# Clock source
set_io clock 20 # friendly name, fpga pin
set_io reset 55 #wrong pin, just holder

# Bus Pirate buffer control pins
set_io bufdir[0] 75 #74LVC1T45 DIR
set_io bufod[0] 73 #74LVC1G07 A
set_io bufio[0] 74 #74LVC1T45 A
set_io bufdir[1] 79
set_io bufod[1] 76
set_io bufio[1] 78
set_io bufdir[2] 82
set_io bufod[2] 80
set_io bufio[2] 81
set_io bufdir[3] 104
set_io bufod[3] 101
set_io bufio[3] 102
set_io bufdir[4] 107
set_io bufod[4] 105
set_io bufio[4] 106

# Peek-behind buffer/latch (74AC573)
set_io lat_oe 91 #latch output enable
set_io lat[0] 93 #mosi
set_io lat[1] 94 #clock
set_io lat[2] 95 #miso
set_io lat[3] 96 #cs
set_io lat[4] 97 #aux0
set_io lat[5] 98 #swv33
set_io lat[6] 99 #swv50
set_io lat[7] 90 # not currently attached!!!!

# Memory controller interface address and data
set_io mc_ce 37 #missing
set_io mc_oe 38 #missing
set_io mc_we 39 #missing

set_io mc_add[0] 3
set_io mc_add[1] 4
set_io mc_add[2] 7
set_io mc_add[3] 8
set_io mc_add[4] 9
set_io mc_add[5] 10

set_io mc_data[0] 24
set_io mc_data[1] 23
set_io mc_data[2] 1
set_io mc_data[3] 2
set_io mc_data[4] 15
set_io mc_data[5] 16
set_io mc_data[6] 17
set_io mc_data[7] 18
set_io mc_data[8] 19
set_io mc_data[9] 25
set_io mc_data[10] 26
set_io mc_data[11] 28
set_io mc_data[12] 29
set_io mc_data[13] 33
set_io mc_data[14] 32
set_io mc_data[15] 31

# Interrupt lines
set_io irq0 129
set_io irq1 128

# SRAM connectons (23LC1024/etc)
set_io sram0_clock 141
set_io sram0_cs 144
set_io sram0_sio[0] 142
set_io sram0_sio[1] 139
set_io sram0_sio[2] 138
set_io sram0_sio[3] 137

set_io sram1_clock 70 
set_io sram1_cs 130
set_io sram1_sio[0] 136
set_io sram1_sio[1] 135
set_io sram1_sio[2] 134
set_io sram1_sio[3] 124 #currently wrong pin! needs to be updated when schematic has updated naming

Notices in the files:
hardware/scratch/BusPirate-ultra-proto-adj_vreg.v.0.brd:
LICENSE: CC-BY-SA
